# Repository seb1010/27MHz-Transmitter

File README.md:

# 27MHz-Transmitter
27.12MHz wiresless transmitter

## Basic flow
* There is a external oscillator that wakes up the MCU a few times every second (allowing MCU to sleep 99.9% of the time) if this is the Nth time the MCU has been woken up it sends a packet
* The MCU powers up the RF chain
* The MCU reads from the sensors then puts this information into a packet
* This packet has ECC added with 255, 154 BCH code. There is an additional framing section added that is not protected by error correction
* The packet is sent out by toggling a gpio pin with 20us bit period
* This waveform is pulse shapped by low pass filters before being sent to the modulator
* The modulated waveform is sent out over the airwaves
* The MCU powers off the board and goes back to sleep

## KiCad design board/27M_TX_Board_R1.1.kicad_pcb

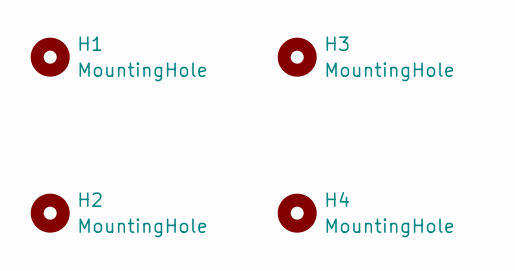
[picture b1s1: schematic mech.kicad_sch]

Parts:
H1, H2, H3, H4: MountingHole; m3_hole_no_copper

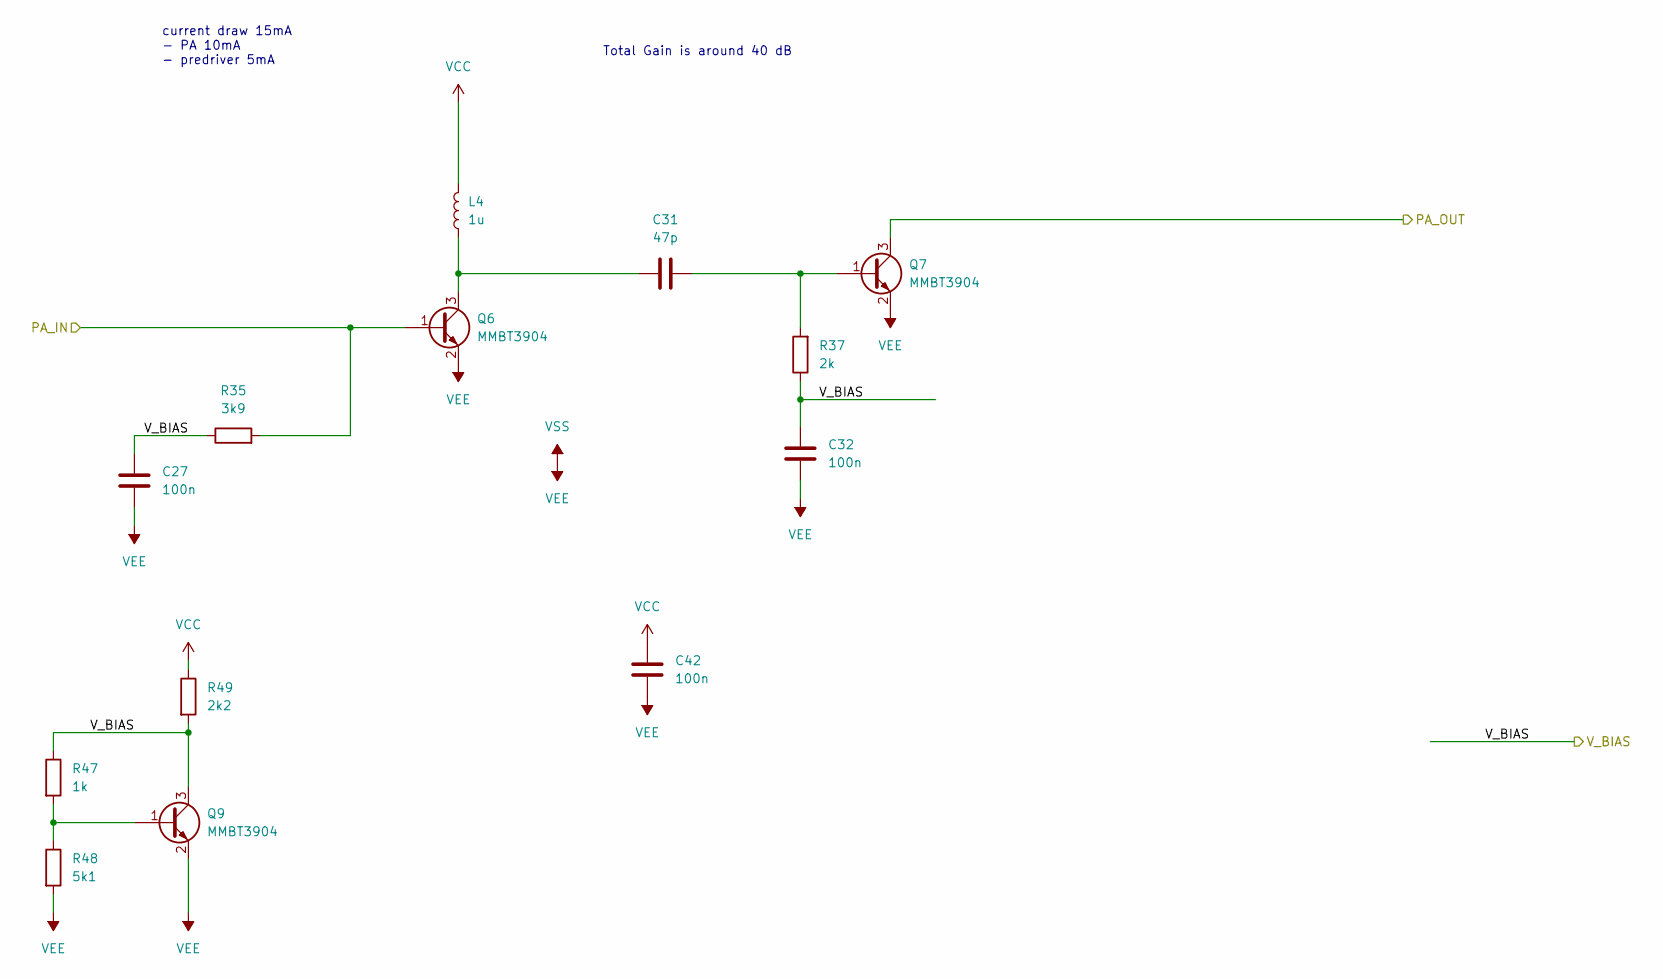
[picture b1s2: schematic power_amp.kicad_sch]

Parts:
C27, C32, C42: 100n; C_0603_1608Metric
C31: 47p; C_0603_1608Metric
L4: 1u; C_0805_2012Metric
Q6, Q7, Q9: MMBT3904; SOT-23
R35: 3k9; C_0603_1608Metric
R37: 2k; C_0603_1608Metric
R47: 1k; C_0603_1608Metric
R48: 5k1; C_0603_1608Metric
R49: 2k2; C_0603_1608Metric

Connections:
/Modulator/MOD_SIG: Q6.1 (B), R35.2; also elsewhere on the board
/Oscillator/V_BIAS: C27.1, C32.1, Q9.3 (C), R35.1, R37.1, R47.1, R49.2; also elsewhere on the board
/Power_Amp/PA_OUT: Q7.3 (C); also elsewhere on the board
unnamed: C31.1, L4.1, Q6.3 (C)
unnamed: C31.2, Q7.1 (B), R37.2
unnamed: Q9.1 (B), R47.2, R48.1
VCC: C42.1, L4.2, R49.1; also elsewhere on the board
VEE: C27.2, C32.2, C42.2, Q6.2 (E), Q7.2 (E), Q9.2 (E), R48.2; also elsewhere on the board

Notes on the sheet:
current draw 15mA - PA 10mA - predriver 5mA
Total Gain is around 40 dB

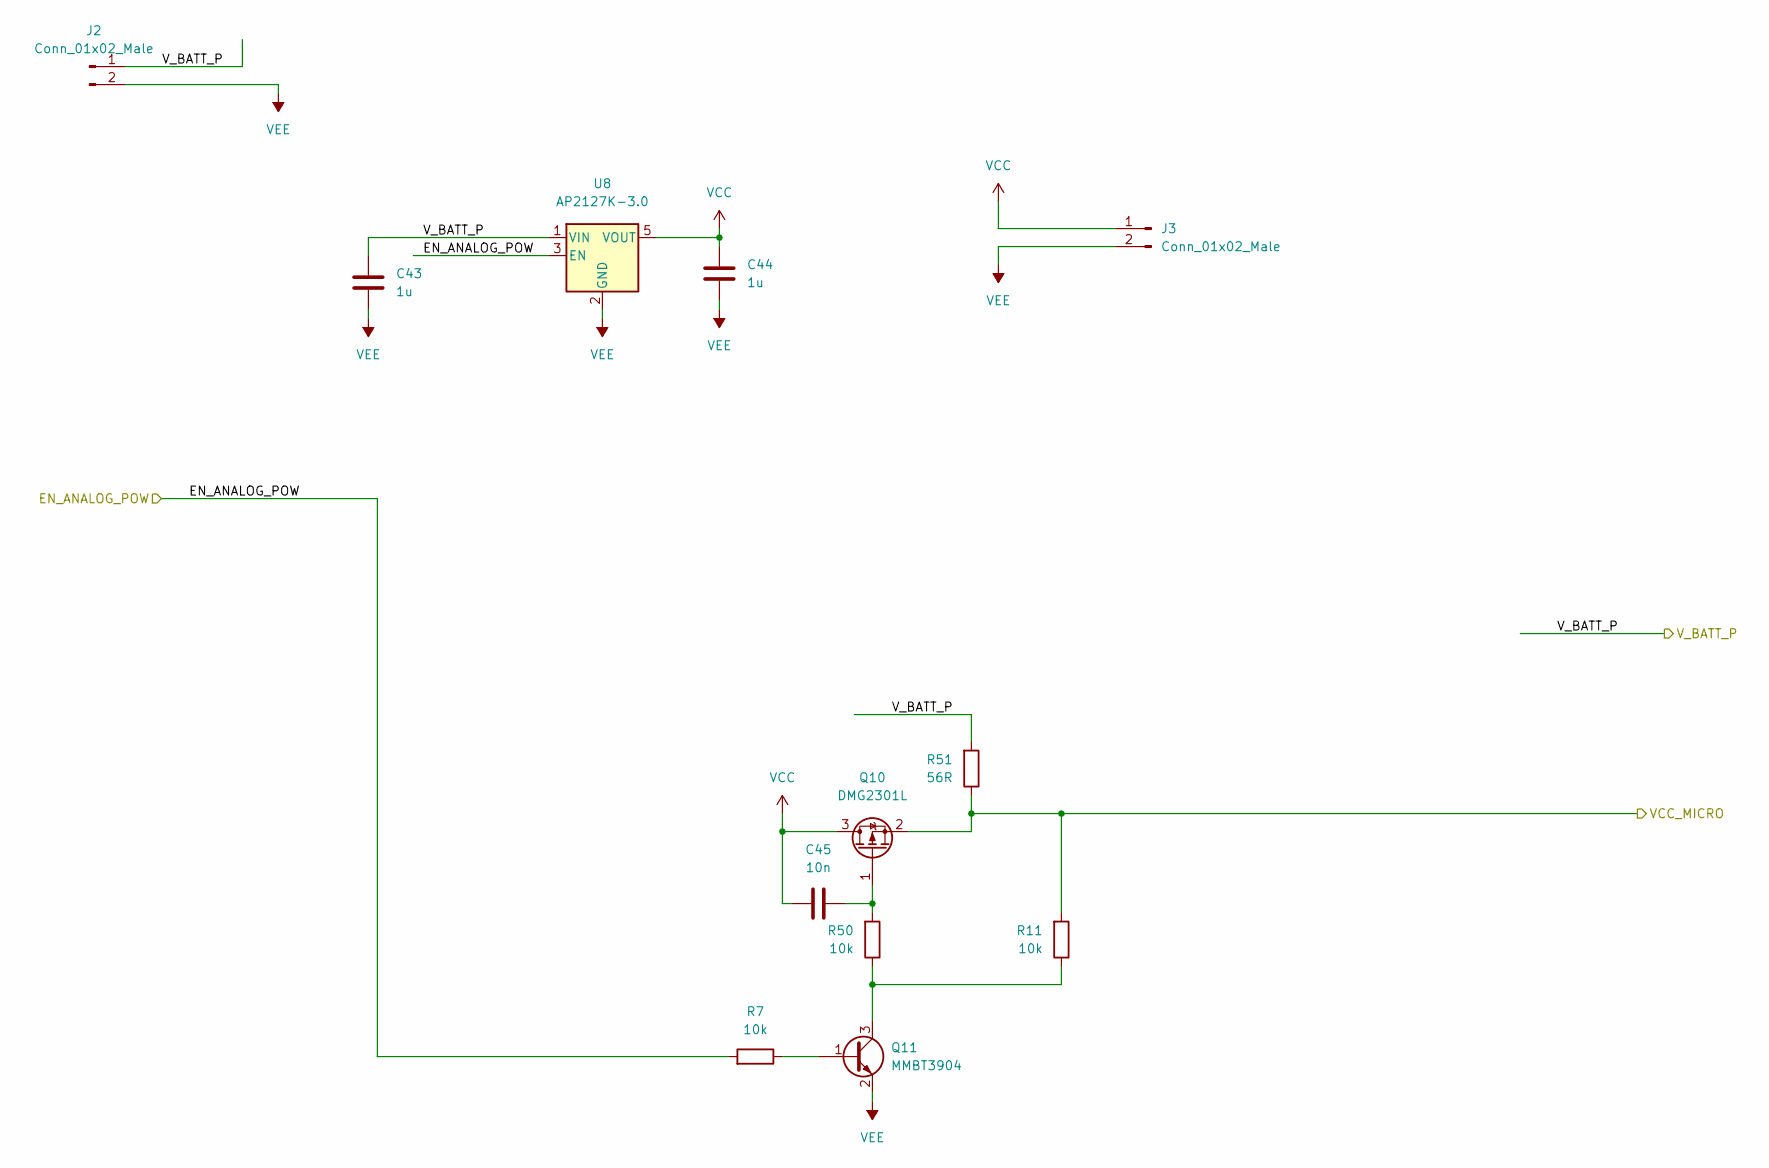
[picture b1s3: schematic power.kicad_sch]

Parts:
C43, C44: 1u; C_0603_1608Metric
C45: 10n; C_0603_1608Metric
J2, J3: Conn_01x02_Male; JST-ZH-2
Q10: DMG2301L; SOT-23
Q11: MMBT3904; SOT-23
R7, R11, R50: 10k; C_0603_1608Metric
R51: 56R; C_0603_1608Metric
U8: AP2127K-3.0; SOT-23-5

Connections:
/Micro/EN_ANALOG_POW: R7.2, U8.3 (EN); also elsewhere on the board
/Micro/VCC_MICRO: Q10.2 (S), R11.2, R51.1; also elsewhere on the board
/Micro/V_BATT_P: C43.1, J2.1, R51.2, U8.1 (VIN); also elsewhere on the board
unnamed: C45.2, Q10.1 (G), R50.2
unnamed: Q11.1 (B), R7.1
unnamed: Q11.3 (C), R11.1, R50.1
VCC: C44.1, C45.1, J3.1, Q10.3 (D), U8.5 (VOUT); also elsewhere on the board
VEE: C43.2, C44.2, J2.2, J3.2, Q11.2 (E), U8.2 (GND); also elsewhere on the board

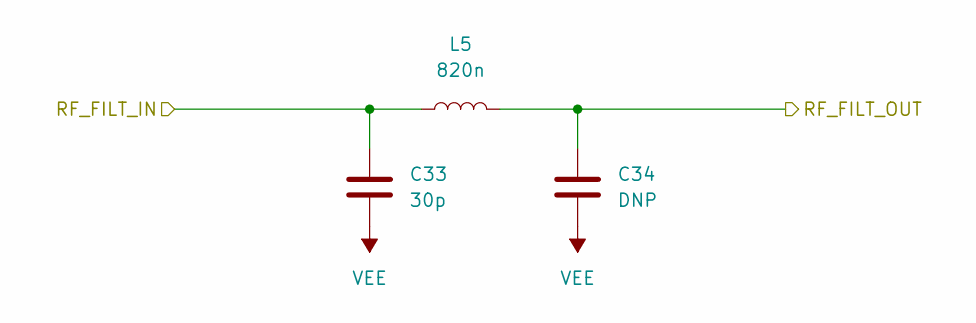
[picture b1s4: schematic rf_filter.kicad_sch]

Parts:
C33: 30p; C_0603_1608Metric
C34: DNP; C_0603_1608Metric
L5: 820n; C_0805_2012Metric

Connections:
/Power_Amp/PA_OUT: C33.1, L5.1; also elsewhere on the board
VCC: C34.1, L5.2; also elsewhere on the board
VEE: C33.2, C34.2; also elsewhere on the board

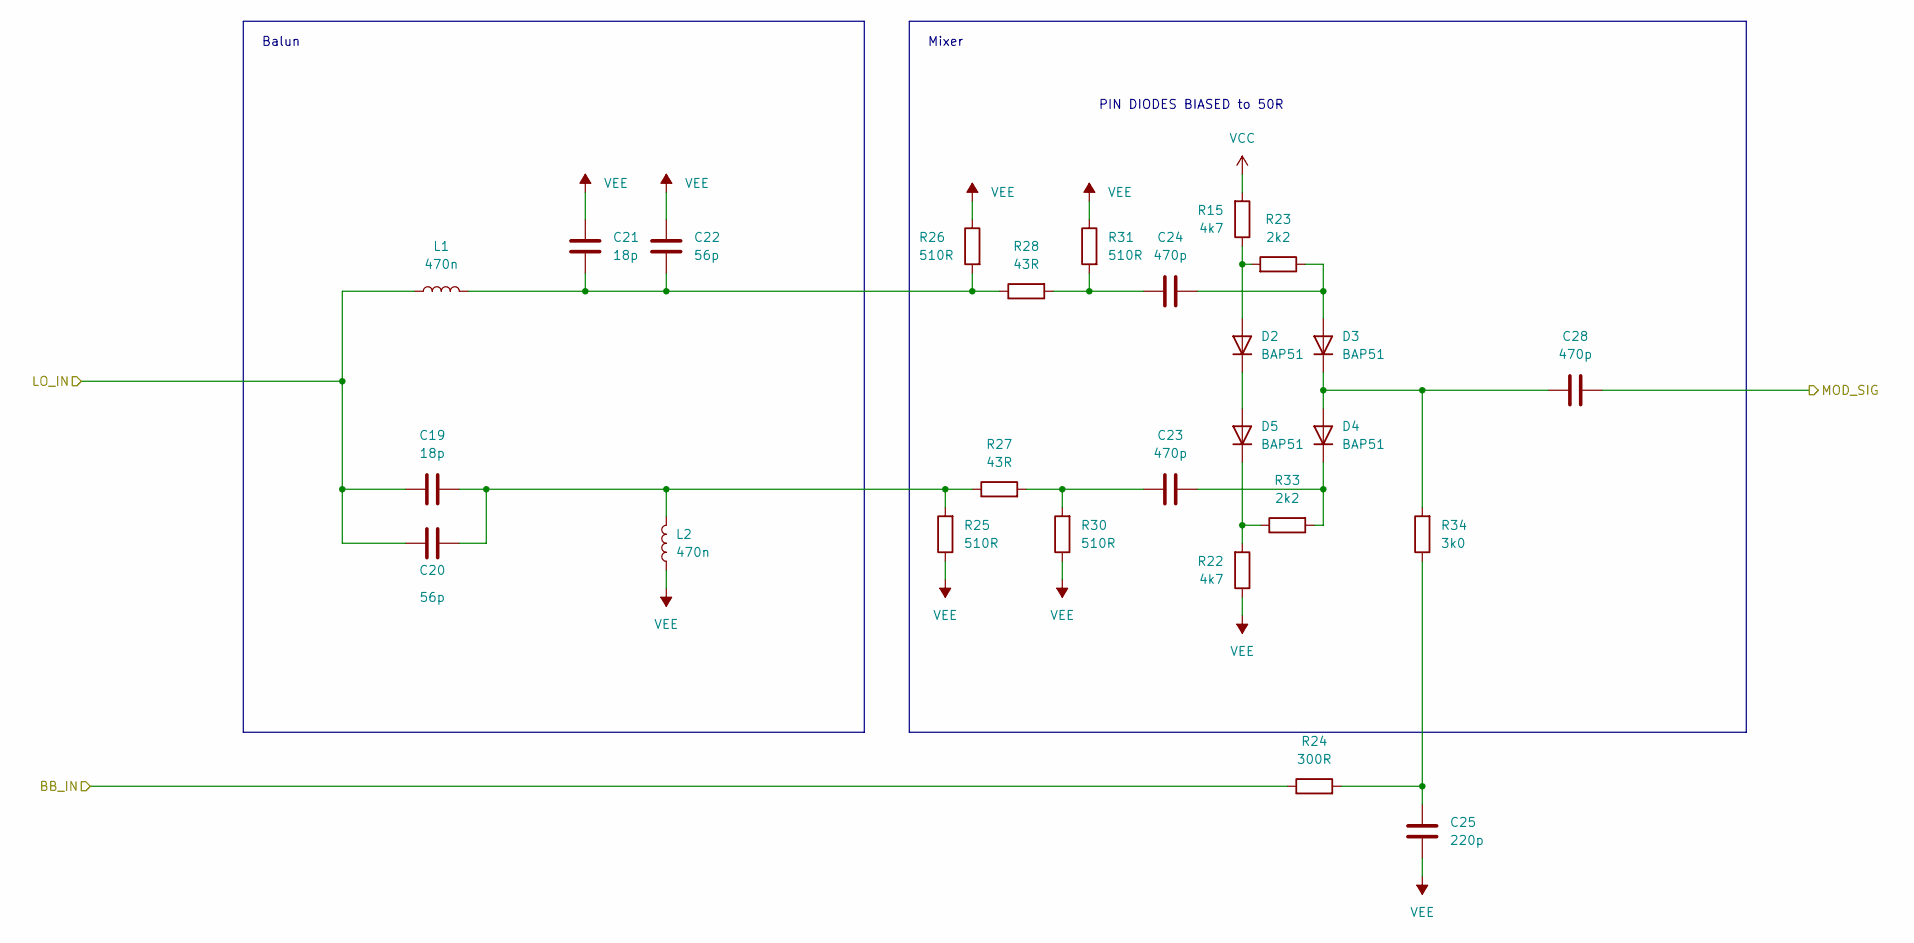
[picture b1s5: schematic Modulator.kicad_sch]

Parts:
C19, C21: 18p; C_0603_1608Metric
C20, C22: 56p; C_0603_1608Metric
C23, C24, C28: 470p; C_0603_1608Metric
C25: 220p; C_0603_1608Metric
D2, D3, D4, D5: BAP51; D_SOD-323
L1, L2: 470n; C_0805_2012Metric
R15, R22: 4k7; C_0603_1608Metric
R23, R33: 2k2; C_0603_1608Metric
R24: 300R; C_0603_1608Metric
R25, R26, R30, R31: 510R; C_0603_1608Metric
R27, R28: 43R; C_0603_1608Metric
R34: 3k0; C_0603_1608Metric

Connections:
/Modulator/BB_IN: R24.1; also elsewhere on the board
/Modulator/LO_IN: C19.1, C20.2, L1.1; also elsewhere on the board
/Modulator/MOD_SIG: C28.2; also elsewhere on the board
unnamed: C19.2, C20.1, L2.2, R25.2, R27.1
unnamed: C21.2, C22.2, L1.2, R26.2, R28.1
unnamed: C23.1, R27.2, R30.2
unnamed: C23.2, D4.1 (K), R33.2
unnamed: C24.1, R28.2, R31.2
unnamed: C24.2, D3.2 (A), R23.1
unnamed: C25.2, R24.2, R34.1
unnamed: C28.1, D3.1 (K), D4.2 (A), R34.2
unnamed: D2.1 (K), D5.2 (A)
unnamed: D2.2 (A), R15.1, R23.2
unnamed: D5.1 (K), R22.2, R33.1
VCC: R15.2; also elsewhere on the board
VEE: C21.1, C22.1, C25.1, L2.1, R22.1, R25.1, R26.1, R30.1, R31.1; also elsewhere on the board

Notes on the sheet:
Balun
Mixer
PIN DIODES BIASED to 50R

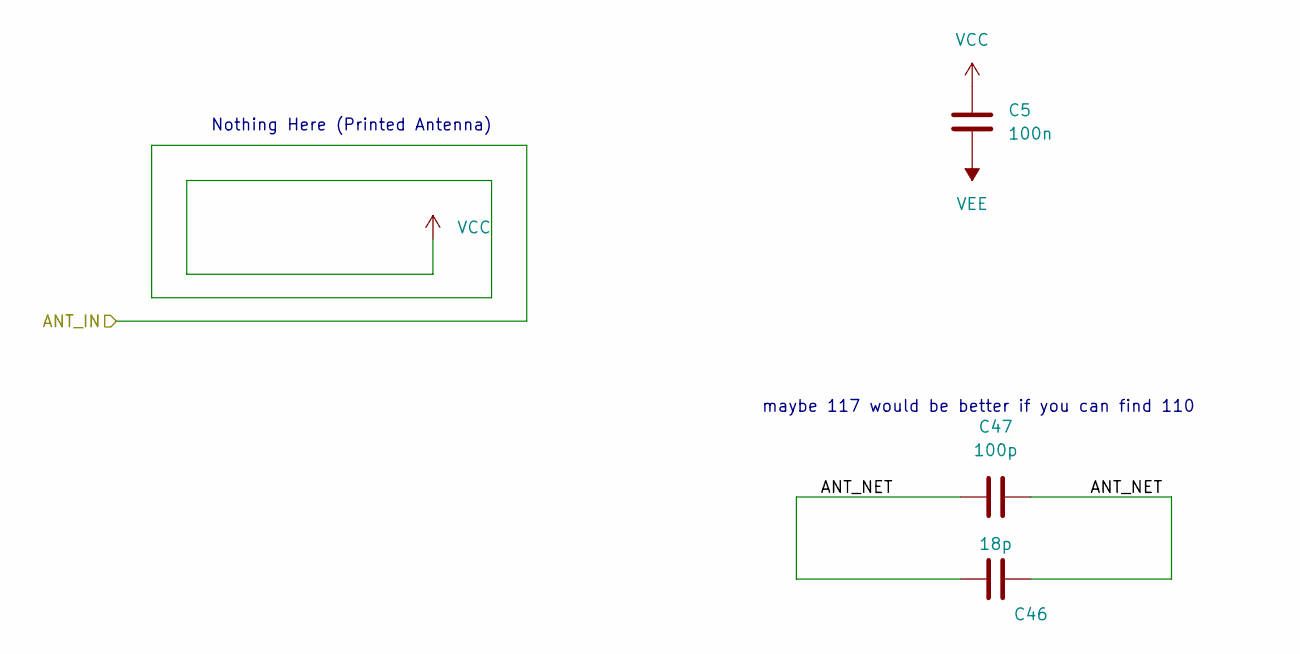
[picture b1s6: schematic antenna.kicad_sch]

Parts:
C5: 100n; C_0603_1608Metric
C46: 18p; C_0603_1608Metric
C47: 100p; C_0603_1608Metric

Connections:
/Antenna/ANT_NET: C46.1, C46.2, C47.1, C47.2
VCC: C5.1; also elsewhere on the board
VEE: C5.2; also elsewhere on the board

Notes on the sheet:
Nothing Here (Printed Antenna)
maybe 117 would be better if you can find 110

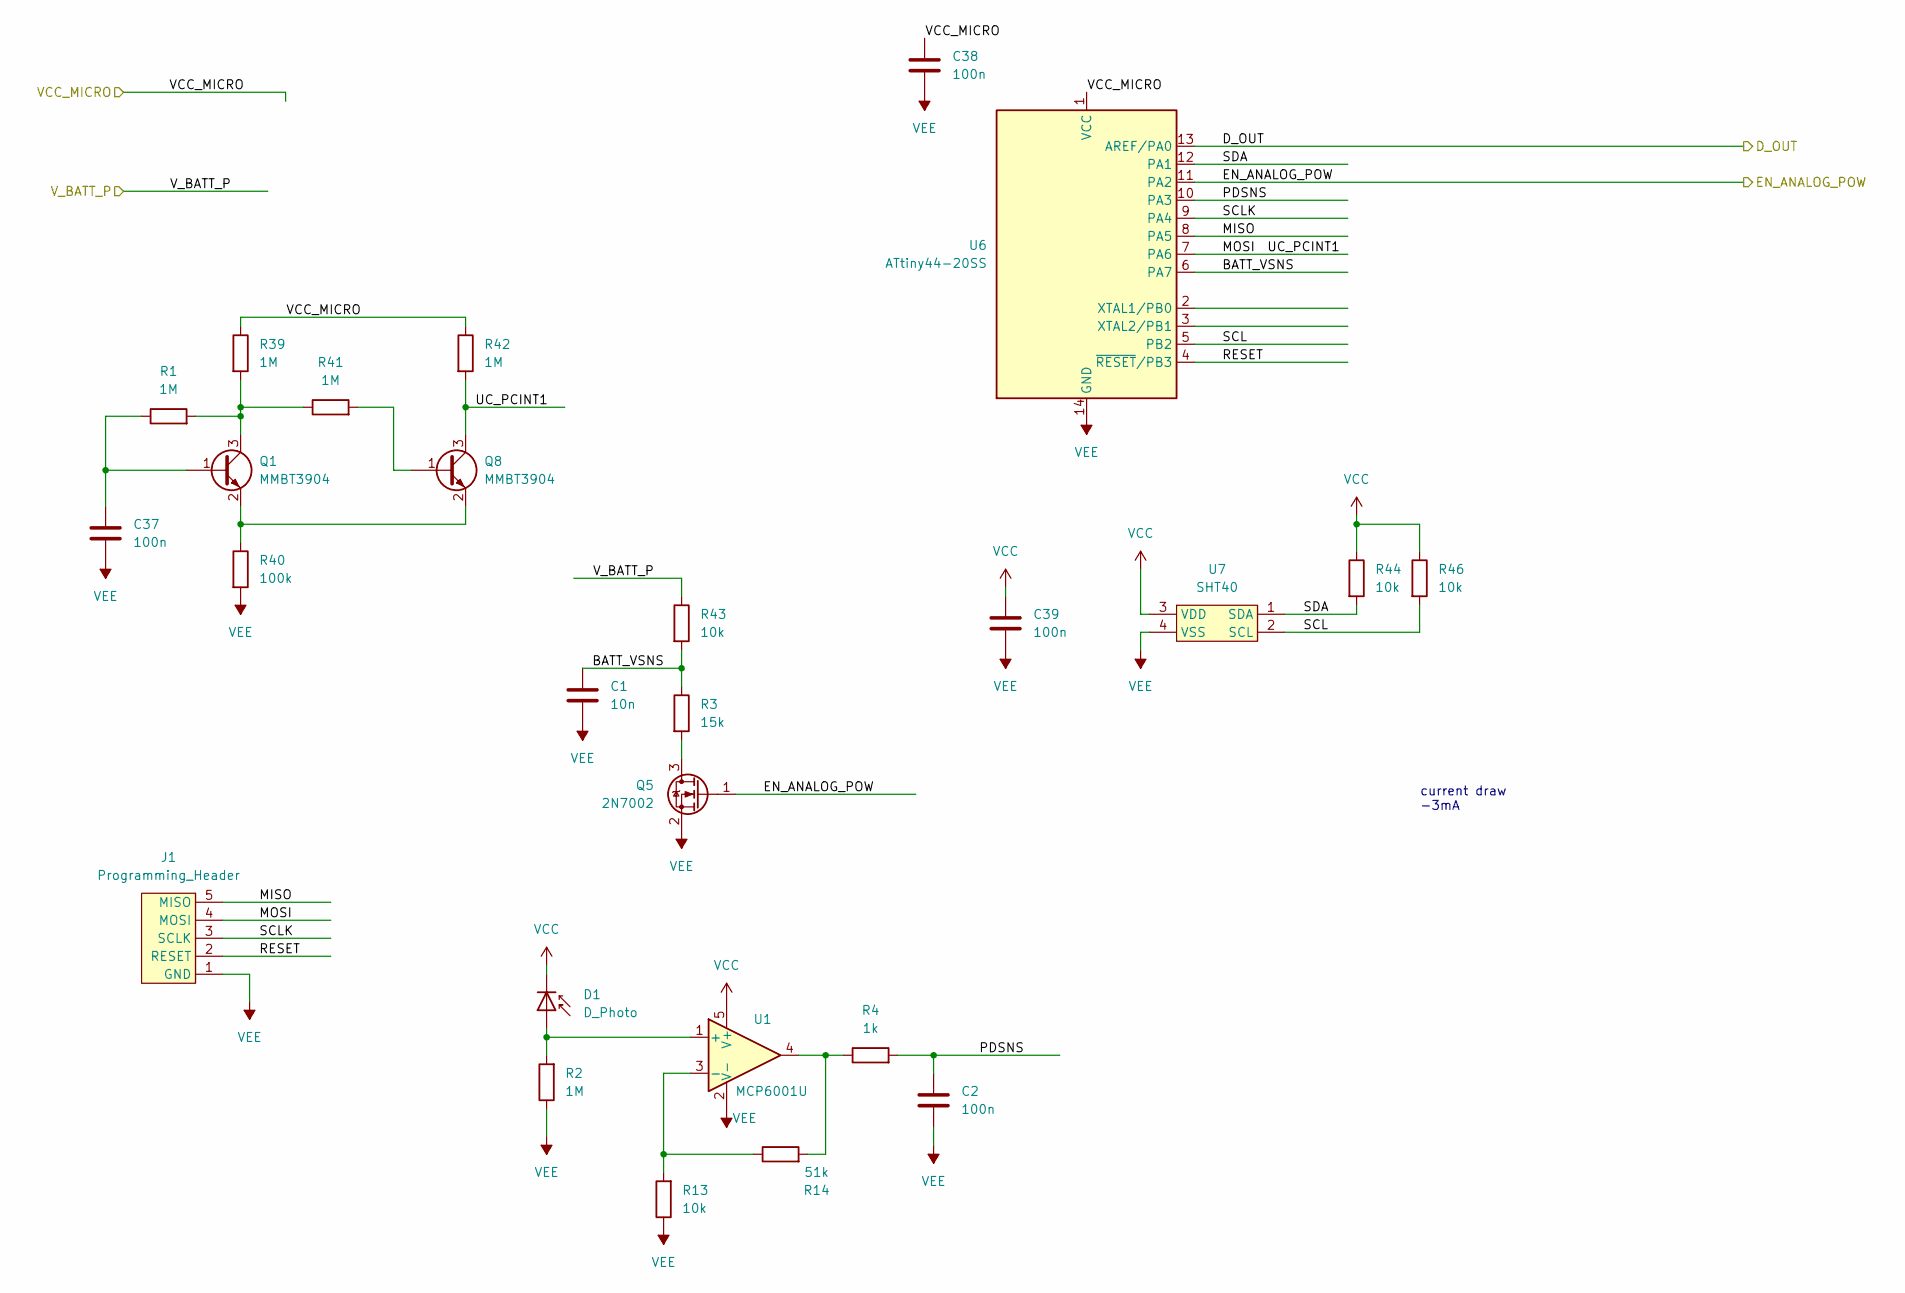
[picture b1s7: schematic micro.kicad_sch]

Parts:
C1: 10n; C_0603_1608Metric
C2, C37, C38, C39: 100n; C_0603_1608Metric
D1: D_Photo; LED_0805_2012Metric
J1: Programming_Header; JST-ZH-5
Q1, Q8: MMBT3904; SOT-23
Q5: 2N7002; SOT-23
R1, R2, R39, R41, R42: 1M; C_0603_1608Metric
R3: 15k; C_0603_1608Metric
R4: 1k; C_0603_1608Metric
R13, R43, R44, R46: 10k; C_0603_1608Metric
R14: 51k; C_0603_1608Metric
R40: 100k; C_0603_1608Metric
U1: MCP6001U; mcp6001
U6: ATtiny44-20SS; SOIC-14_3.9x8.7mm_P1.27mm
U7: SHT40

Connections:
/Micro/BATT_VSNS: C1.1, R3.1, R43.2, U6.6 (PA7)
/Micro/D_OUT: U6.13 (AREF/PA0); also elsewhere on the board
/Micro/EN_ANALOG_POW: Q5.1 (G), U6.11 (PA2); also elsewhere on the board
/Micro/MISO: J1.5 (MISO), U6.8 (PA5)
/Micro/MOSI: J1.4 (MOSI), Q8.3 (C), R42.2, U6.7 (PA6)
/Micro/PDSNS: C2.1, R4.2, U6.10 (PA3)
/Micro/RESET: J1.2 (RESET), U6.4 (~RESET/PB3)
/Micro/SCL: R46.2, U6.5 (PB2), U7.2 (SCL)
/Micro/SCLK: J1.3 (SCLK), U6.9 (PA4)
/Micro/SDA: R44.2, U6.12 (PA1), U7.1 (SDA)
/Micro/VCC_MICRO: C38.1, R39.1, R42.1, U6.1 (VCC); also elsewhere on the board
/Micro/V_BATT_P: R43.1; also elsewhere on the board
unnamed: C37.1, Q1.1 (B), R1.1
unnamed: D1.2 (A), R2.2, U1.1 (+)
unnamed: Q1.2 (E), Q8.2 (E), R40.1
unnamed: Q1.3 (C), R1.2, R39.2, R41.1
unnamed: Q5.3 (D), R3.2
unnamed: Q8.1 (B), R41.2
unnamed: R13.2, R14.1, U1.3 (-)
unnamed: R4.1, R14.2, U1.4
VCC: C39.1, D1.1 (K), R44.1, R46.1, U1.5 (V+), U7.3 (VDD); also elsewhere on the board
VEE: C1.2, C2.2, C37.2, C38.2, C39.2, J1.1 (GND), Q5.2 (S), R2.1, R13.1, R40.2, U1.2 (V-), U6.14 (GND), U7.4 (VSS); also elsewhere on the board

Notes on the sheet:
current draw -3mA

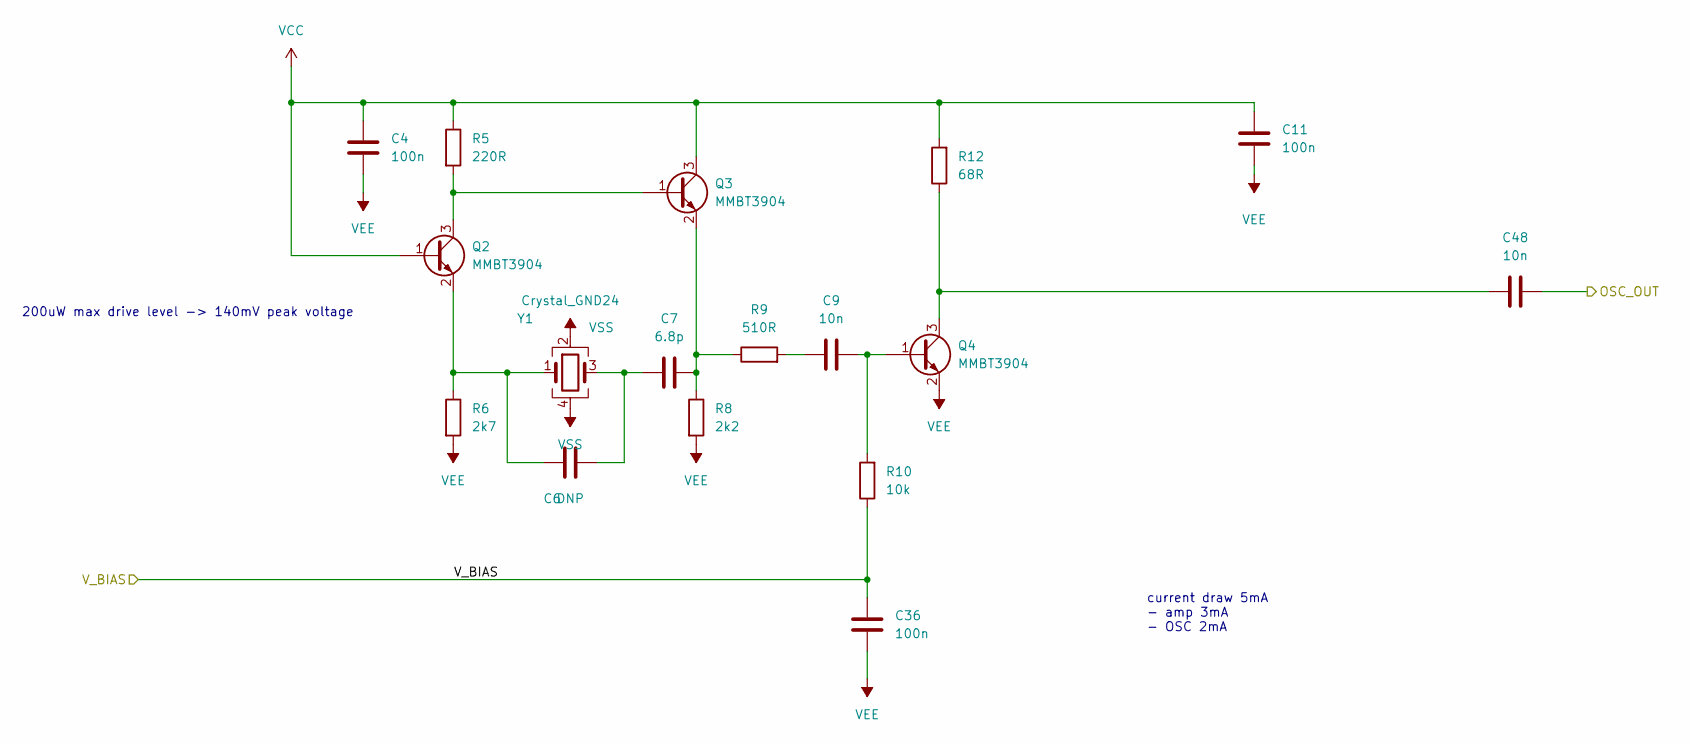
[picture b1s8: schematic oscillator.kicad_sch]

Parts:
C4, C11, C36: 100n; C_0603_1608Metric
C6: DNP; C_0603_1608Metric
C7: 6.8p; C_0603_1608Metric
C9, C48: 10n; C_0603_1608Metric
Q2, Q3, Q4: MMBT3904; SOT-23
R5: 220R; C_0603_1608Metric
R6: 2k7; C_0603_1608Metric
R8: 2k2; C_0603_1608Metric
R9: 510R; C_0603_1608Metric
R10: 10k; C_0603_1608Metric
R12: 68R; C_0603_1608Metric
Y1: Crystal_GND24; RH100

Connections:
/Modulator/LO_IN: C48.1; also elsewhere on the board
/Oscillator/V_BIAS: C36.1, R10.1; also elsewhere on the board
unnamed: C6.1, C7.2, Y1.3
unnamed: C6.2, Q2.2 (E), R6.1, Y1.1
unnamed: C7.1, Q3.2 (E), R8.1, R9.1
unnamed: C9.1, Q4.1 (B), R10.2
unnamed: C9.2, R9.2
unnamed: C48.2, Q4.3 (C), R12.1
unnamed: Q2.3 (C), Q3.1 (B), R5.2
VCC: C4.2, C11.2, Q2.1 (B), Q3.3 (C), R5.1, R12.2; also elsewhere on the board
VEE: C4.1, C11.1, C36.2, Q4.2 (E), R6.2, R8.2, Y1.2, Y1.4; also elsewhere on the board

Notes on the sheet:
current draw 5mA - amp 3mA - OSC 2mA
200uW max drive level -> 140mV peak voltage

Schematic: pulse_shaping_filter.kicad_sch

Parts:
C13, C16: 390p; C_0603_1608Metric
C14, C15: 160p; C_0603_1608Metric
C26, C29: 100n; C_0603_1608Metric
R16, R17, R54: 2k; C_0603_1608Metric
R18, R19, R20, R21: 20k; C_0603_1608Metric
U2, U3: MCP6001U; mcp6001

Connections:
/Micro/D_OUT: R16.1; also elsewhere on the board
/Modulator/BB_IN: C16.2, U3.3 (-), U3.4; also elsewhere on the board
unnamed: C13.1, R18.2, R19.1
unnamed: C13.2, R20.1, U2.3 (-), U2.4
unnamed: C14.1, R19.2, U2.1 (+)
unnamed: C15.1, R21.2, U3.1 (+)
unnamed: C16.1, R20.2, R21.1
unnamed: R16.2, R17.1, R18.1, R54.2
VCC: C26.1, C29.1, R54.1, U2.5 (V+), U3.5 (V+); also elsewhere on the board
VEE: C14.2, C15.2, C26.2, C29.2, R17.2, U2.2 (V-), U3.2 (V-); also elsewhere on the board

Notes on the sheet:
Current draw 1mA

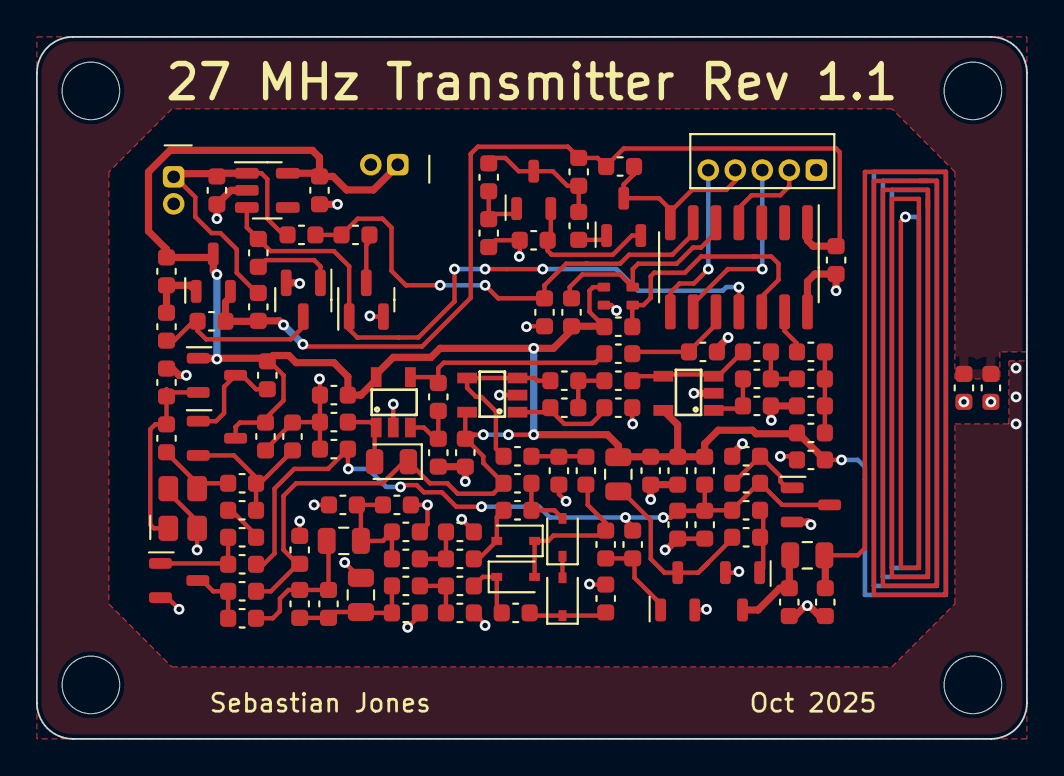
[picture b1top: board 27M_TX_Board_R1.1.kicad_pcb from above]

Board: 2 copper layers, 55.0 x 39.0 mm, 119 parts (0 on the bottom side), 58 nets.

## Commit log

2026-01-01 adding stuff
2026-01-01 adding pdf
